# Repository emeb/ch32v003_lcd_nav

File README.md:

# ch32v003_lcd_nav
A simple CH32V003 board with IPS LCD and navigation switch.

## Abstract
This is a board with the following features:
* CH32V003F4P6 RISC-V MCU in TSSOP20 package
* 160x80 IPS LCD display
* 5-way navigation switch
* USB socket with power and optional low-speed interface
* Qwiic jack for I2C interfacing

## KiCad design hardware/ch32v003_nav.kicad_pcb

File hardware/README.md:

# Hardware Design
This directory contains the KiCad 8.09 design files for the ch32v003_nav board
design.

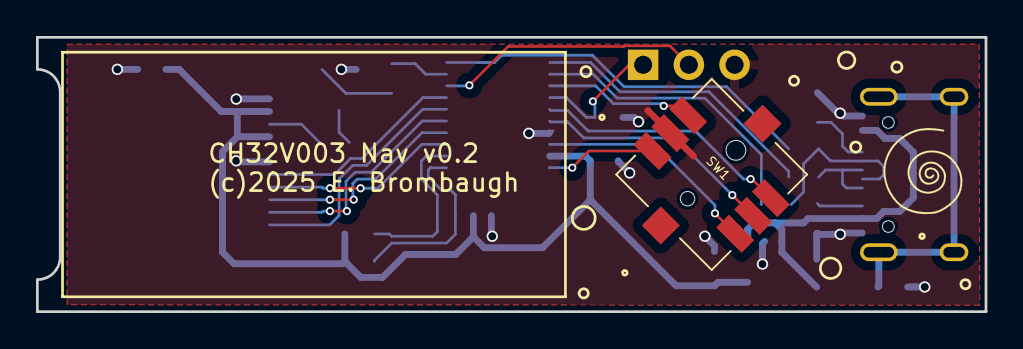
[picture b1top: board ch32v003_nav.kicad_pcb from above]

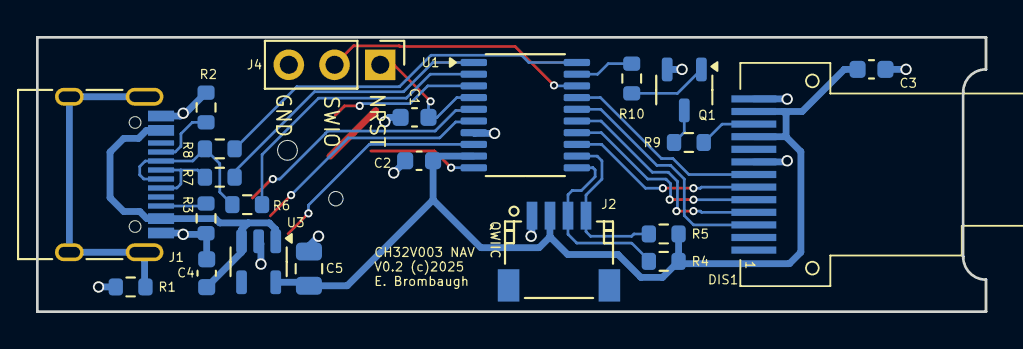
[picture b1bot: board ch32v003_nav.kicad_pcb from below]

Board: 2 copper layers, 52.7 x 15.2 mm, 24 parts (22 on the bottom side), 29 nets.

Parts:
C1, C2, C3: 0.1uf; C_0603_1608Metric
C4: 1uf; C_0603_1608Metric
C5: 10uf; C_0805_2012Metric
DIS1: 0.96_IPS_TFT_LCD
J1: USB_C_Receptacle_USB2.0; USB_C_Receptacle_HRO_TYPE-C-31-M-12
J2: JST SH-4 (Qwiic); JST_SH_SM04B-SRSS-TB_04x1.00mm_Angled
J4: Conn_01x03_Pin; PinHeader_1x03_P2.54mm_Vertical
Q1: DMN63D8L; SOT-23-3
R1: 1M; R_0603_1608Metric
R2, R3: 5k1; R_0603_1608Metric
R4, R5: 4k7; R_0603_1608Metric
R6: 1.5k; R_0603_1608Metric
R7, R8: 22; R_0603_1608Metric
R9: 100; R_0603_1608Metric
R10: 1k; R_0603_1608Metric
Ref**: Val**; avatar_small
SW1: nav_5way
U1: CH32V003F4P6; TSSOP-20_4.4x6.5mm_P0.65mm
U3: XC6222B331MR-G; SOT-23-5

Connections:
+3.3V: C2.1, C3.1, C5.1, DIS1.10 (VCC), DIS1.12 (LEDA), J2.2, R4.2, R5.2, U1.9 (VDD), U3.5 (VOUT)
/JS_CTR: SW1.5 (CTR), U1.6 (PA2)
/JS_NE: SW1.6 (NE), U1.5 (PA1)
/JS_NW: SW1.1 (NW), U1.3 (PD6)
/JS_SE: SW1.4 (SE), U1.8 (PD0)
/JS_SW: SW1.3 (SW), U1.10 (PC0)
/LCD_BKL: R10.2, U1.19 (PD2)
/LCD_CS: DIS1.7 (CS), U1.17 (PC7)
/LCD_D/C: DIS1.5 (RS), U1.14 (PC4)
/LCD_MOSI: DIS1.3 (SDA), U1.16 (PC6)
/LCD_NRST: DIS1.6 (RES), U1.13 (PC3)
/LCD_SCLK: DIS1.4 (SCL), U1.15 (PC5)
/NRST: C1.1, J4.1, U1.4 (PD7)
/SCL: J2.4, R5.1, U1.12 (PC2)
/SDA: J2.3, R4.1, U1.11 (PC1)
/SWIO: J4.2, U1.18 (PD1)
/USB_DM: R8.1, U1.20 (PD3)
/USB_DP: R7.1, U1.1 (PD4)
/USB_DPU: R6.1, U1.2 (PD5)
/VUSB: C4.1, J1.A4 (VBUS), J1.A9 (VBUS), J1.B4 (VBUS), J1.B9 (VBUS), U3.1 (VIN), U3.3 (CE)
GND: C1.2, C2.2, C3.2, C4.2, C5.2, DIS1.8 (GND), DIS1.13 (GND), J1.A1 (GND), J1.A12 (GND), J1.B1 (GND), J1.B12 (GND), J2.1, J4.3, Q1.2 (S), R1.1, R2.1, R3.1, SW1.2 (COM), U1.7 (VSS), U3.2 (GND)
unnamed: DIS1.11 (LEDK), R9.2
unnamed: J1.A5 (CC1), R2.2
unnamed: J1.B5 (CC2), R3.2
unnamed: J1.A6 (D+), J1.B6 (D+), R7.2
unnamed: J1.A7 (D-), J1.B7 (D-), R6.2, R8.2
unnamed: J1.S1 (SHIELD), R1.2
unnamed: Q1.3 (D), R9.1
unnamed: Q1.1 (G), R10.1

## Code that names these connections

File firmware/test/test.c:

/*
 * test nav button & LCD
 * 04-29-2025 E. Brombaugh
 */
 
/*
 * Pin assignments for 20-pin package
 * Pin # | GPIO     | Signal   | Function
 *  1      PD4        USB_DP     USB Data +
 *  2      PD5        USB_DPU    USB pullup
 *  3      PD6    	  JS_NW      Joystick NW switch
 *  4      PD7    	  NRST       Low-true reset
 *  5      PA1        JS_NE		 Joystick NE switch
 *  6      PA2   	  JS_CTR	 Joystick Center switch
 *  7      VSS        GND		 Power
 *  8      PD0        JS_SE      Joystick SE switch
 *  9      VDD        +3.3V      Power
 *  10     PC0        JS_SW      Joystick SW switch
 *  11     PC1        SDA        I2C data / piezo
 *  12     PC2        SCL        I2C clock / piezo 
 *  13     PC3        LCD_NRST   Display low-rtue reset
 *  14     PC4        LCD_D/C    Display cmd/data 
 *  15     PC5        LCD_SCLK   Display serial clock
 *  16     PC6        LCD_MOSI   Display serial data
 *  17     PC7        LCD_CS     Display select 
 *  18     PD1        SWIO       Programmer 
 *  19     PD2        LCD_BKL    Display backlight 
 *  20     PD3        USB_DM     USB Data - 
 */

/* uncomment this to try pwm hue */
#define HUE

#include "ch32fun.h"
#include <stdio.h>
#include <string.h>
#include "systick.h"
#include "gfx.h"
#include "lcd.h"
#include "rand.h"

/* build version in simple format */
const char *fwVersionStr = "V1.0";

/* build time */
const char *bdate = __DATE__;
const char *btime = __TIME__;

/* key to char mapping */
const char keychar[] =
{
	24,	// up
	26, // right
	4,	// center
	25,	// down
	27,	// left
};

/* key locations */
#define XCTR 80
#define YCTR 40
#define SPACING 26
#define RADIUS 10
const int16_t keyloc[] =
{
	XCTR, YCTR-SPACING,	// up
	XCTR+SPACING, YCTR,	// right
	XCTR, YCTR,			// center
	XCTR, YCTR+SPACING,	// down
	XCTR-SPACING, YCTR,	// left
};

/*
 * Start here
 */
int main()
{
	char textbuf[16];
	
	// setup basic stuff - clocks, serial, etc
	SystemInit();

	// start serial @ default 115200bps
	Delay_Ms( 100 );
	printf("\r\r\n\nTest Nav button and LCD\n\r");
	printf("Version: %s\n\r", fwVersionStr);
	printf("Build Date: %s\n\r", bdate);
	printf("Build Time: %s\n\r", btime);
	
	/* init systick */
	systick_init();
	printf("initialized systick IRQ\n\r");
	
	/* init lcd */
	gfx_init(&ST7735_drvr);
	printf("initialized graphics & LCD\n\r");
#if 0
	lcd_bkl(1);
#if 0
	printf("line test\n\r");
	gfx_set_forecolor(GFX_WHITE);
	gfx_drawline(0, 0, 159, 79);
	gfx_drawline(0, 79, 159, 0);
	gfx_set_forecolor(GFX_MAGENTA);
	gfx_drawstrctr(80, 40-4, "Hello World!");
#else
	printf("Font Test\n\r");
	gfx_set_forecolor(GFX_WHITE);
	for(int x=0;x<20;x++)
	{
		for(int y=0;y<10;y++)
		{
			gfx_drawchar(x*8,y*8,y*20+x);
		}
	}
#endif
	printf("waiting...\n\r");
	while(1) {}
#else
	gfx_clrscreen();
#endif
	lcd_bkl(1);
	

	while(1)
	{
		/* random text bubbles */
		GFX_COLOR color = rand()&0xffffff;
		gfx_set_forecolor(color);
		int16_t x = rand() % 160;
		int16_t y = rand() % 80;
		gfx_fillcircle(x, y, 15);
		gfx_set_forecolor(GFX_WHITE);
		gfx_set_backcolor(color);
		gfx_drawstrctr(x, y-4, "Hi");
		
		/* test buttons */
		gfx_set_txtscale(2);
		gfx_set_backcolor(GFX_BLACK);
		for(int i=0;i<NUM_BTNS;i++)
		{
			if(SysTick_get_button(i))
			{
				printf("%s\n\r", btn_name[i]);
				gfx_set_forecolor(GFX_BLACK);
				gfx_fillcircle(keyloc[2*i], keyloc[2*i+1], RADIUS);
				gfx_set_forecolor(GFX_WHITE);
				gfx_drawchar(keyloc[2*i]-8, keyloc[2*i+1]-8, keychar[i]);
			}
		}
		gfx_set_txtscale(1);
		
		Delay_Ms(100);
	}
}

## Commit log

2025-05-17 Create LICENSE
2025-05-17 Initial commit of board and demo firmware
2025-05-17 Updated for latest ch32fun
2025-05-17 Add firmware README
2025-05-27 Renamed & improved to run on working hardware.
2025-05-27 remove merge crud
2025-05-27 added photographs
2025-05-28 Add a test application
2025-05-28 remove dangling junk
2025-05-28 Added link to rv003usb demo
2025-05-28 fix link formatting

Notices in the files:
hardware/ch32v003_nav.kicad_pcb:
V0.2 (c)2025
(c)2025 E. Brombaugh
